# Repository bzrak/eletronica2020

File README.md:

# Eletrônica para Computação
Projects for SSC180 - Eletrônica para Computação

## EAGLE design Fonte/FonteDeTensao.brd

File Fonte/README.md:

# Projeto 1- Fonte de Tensão 12V

Projeto para a disciplina SSC0180-Eletrônica para Computação no Instituto de Ciências Matemáticas e de Computação (ICMC-USP)

## Especificações

> Fonte de Tensão entre 3V a 12V com capacidade de 100mA

## Componentes

| Componente                                                   | Preço    |
| ------------------------------------------------------------ | -------- |
| 1x [Transformador](https://www.baudaeletronica.com.br/transformador-trafo-12v-12v-500ma-110-220vac.html) | R$ 23,40 |
| 1x [Capacitor 470uF](https://www.baudaeletronica.com.br/capacitor-eletrolitico-470uf-25v.html) | R$ 0,35  |
| 1x [Resistor 1k](https://www.baudaeletronica.com.br/resistor-1k-5-1-4w.html) | R$ 0,08  |
| 1x [Resistor 5k1](https://www.baudaeletronica.com.br/resistor-5k1-5-1-4w.html) | R$ 0,08  |
| 1x [Potenciometro 10k](https://www.baudaeletronica.com.br/potenciometro-linear-de-10k-10000.html) | R$ 1,54  |
| 1x [Resistor 3k3](https://www.baudaeletronica.com.br/resistor-3k3-1-2w.html) | R$ 0,15  |
| 1x [Zener 13V](https://www.baudaeletronica.com.br/diodo-zener-1n4743-13v-1w.html) | R$ 0,21  |
| 4x [Diodo](https://www.baudaeletronica.com.br/diodo-1n4007.html) | R$ 0,48  |
| 1x [Transistor NPN](https://www.baudaeletronica.com.br/transistor-npn-bc337.html) | R$ 0,18  |
| **TOTAL**                                                    | R$ 26,47 |

## Circuito

### Falstad:

- http://tinyurl.com/y7hu6ace

### Esquemático:

### PCB:

## Video Explicativo do Circuito:
https://www.youtube.com/watch?v=7D-wKa_Jvzw

# Feito por
Bernardo Azrak Nardelli - 11925194

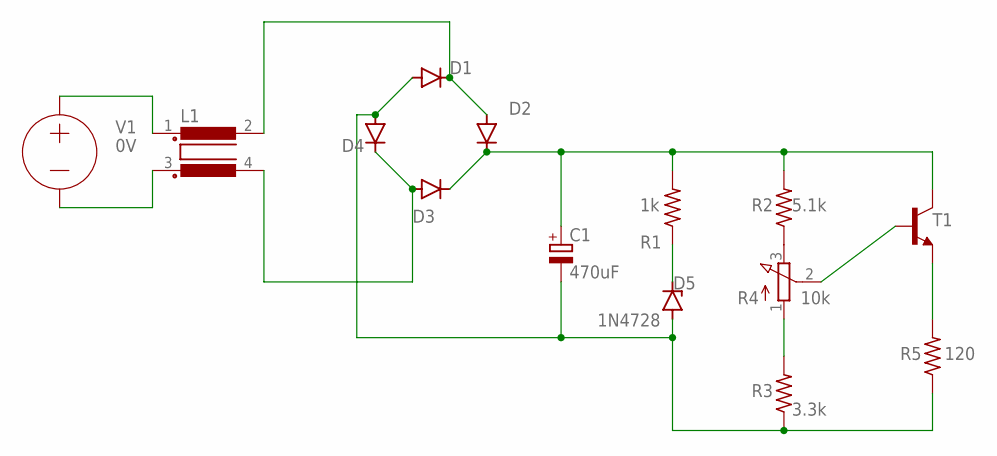
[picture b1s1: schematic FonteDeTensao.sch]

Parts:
C1: 470uF; E2,5-6E
D1, D2, D3, D4: 1N4004; DO41-10
D5: 1N4728; DO41Z10
L1: R1405VB1; B1
R1: 1k; 0411/12
R2: 5.1k; 0411/12
R3: 3.3k; 0411/12
R4: 10k; 3RP/1610N
R5: 120; 0411/12
T1: BC337-16-NPN-TO92-CBE; TO92-CBE

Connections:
unnamed: D1.C, D2.A, L1.2
unnamed: C1.+, D2.C, D3.C, R1.2, R2.2, T1.C
unnamed: D3.A, D4.C, L1.4
unnamed: C1.-, D1.A, D4.A, D5.A, R3.1, R5.1
unnamed: R2.1, R3.2, R4.1 (A), R4.2 (S), R4.3 (E), T1.B
unnamed: D5.C, R1.1
unnamed: R5.2, T1.E

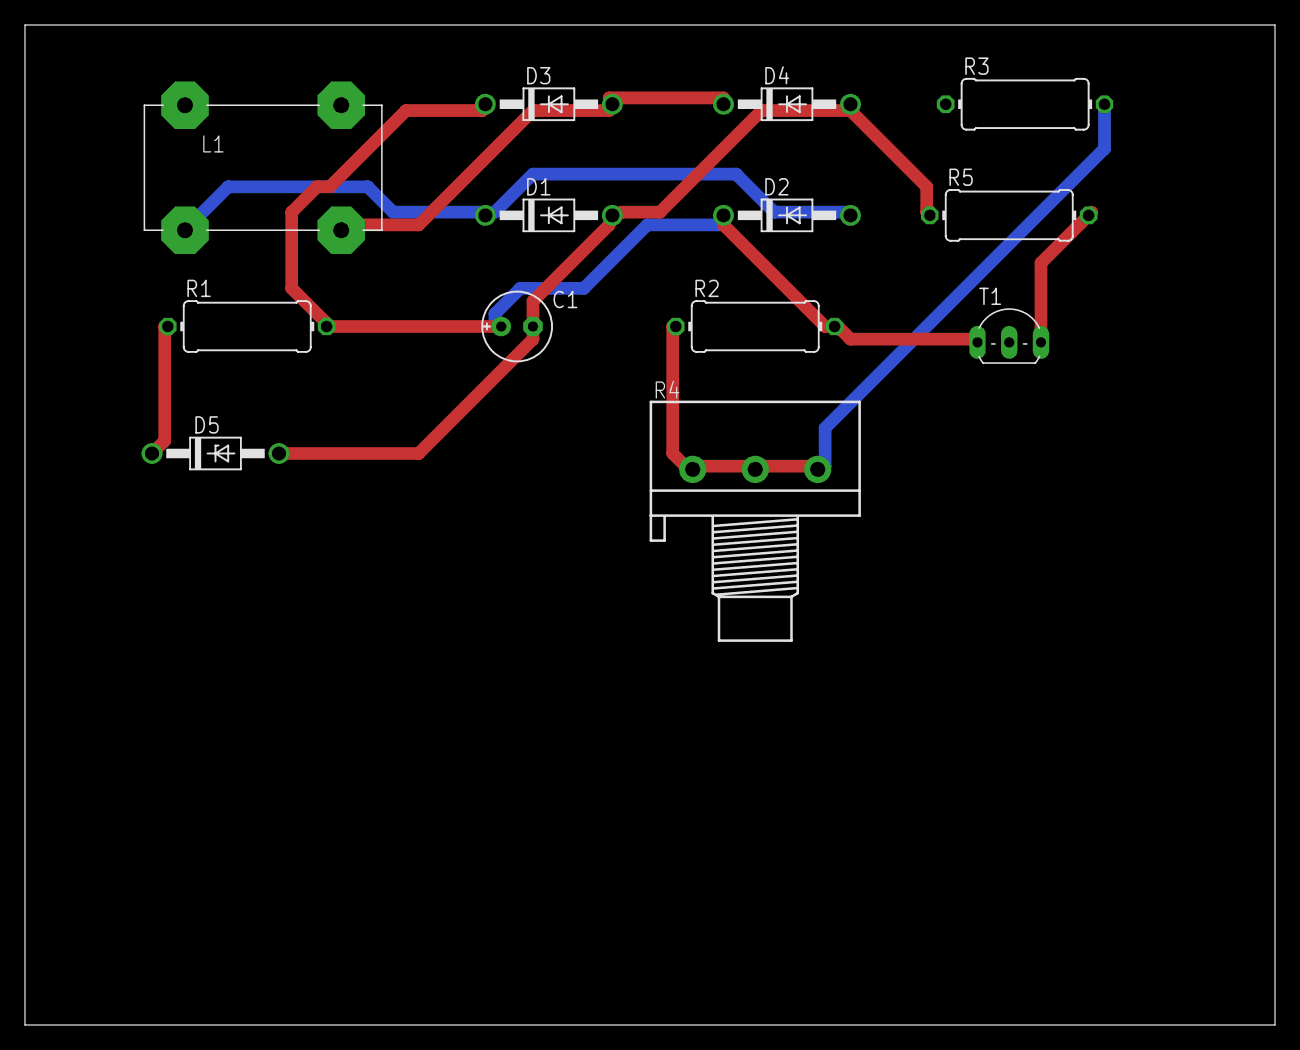
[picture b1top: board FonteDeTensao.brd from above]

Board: 2 copper layers, 100.0 x 80.0 mm, 13 parts (0 on the bottom side), 7 nets.
